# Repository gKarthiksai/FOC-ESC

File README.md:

# FOC-ESC
This is a FOC based ESC designed using open source PCB design software KiCad.

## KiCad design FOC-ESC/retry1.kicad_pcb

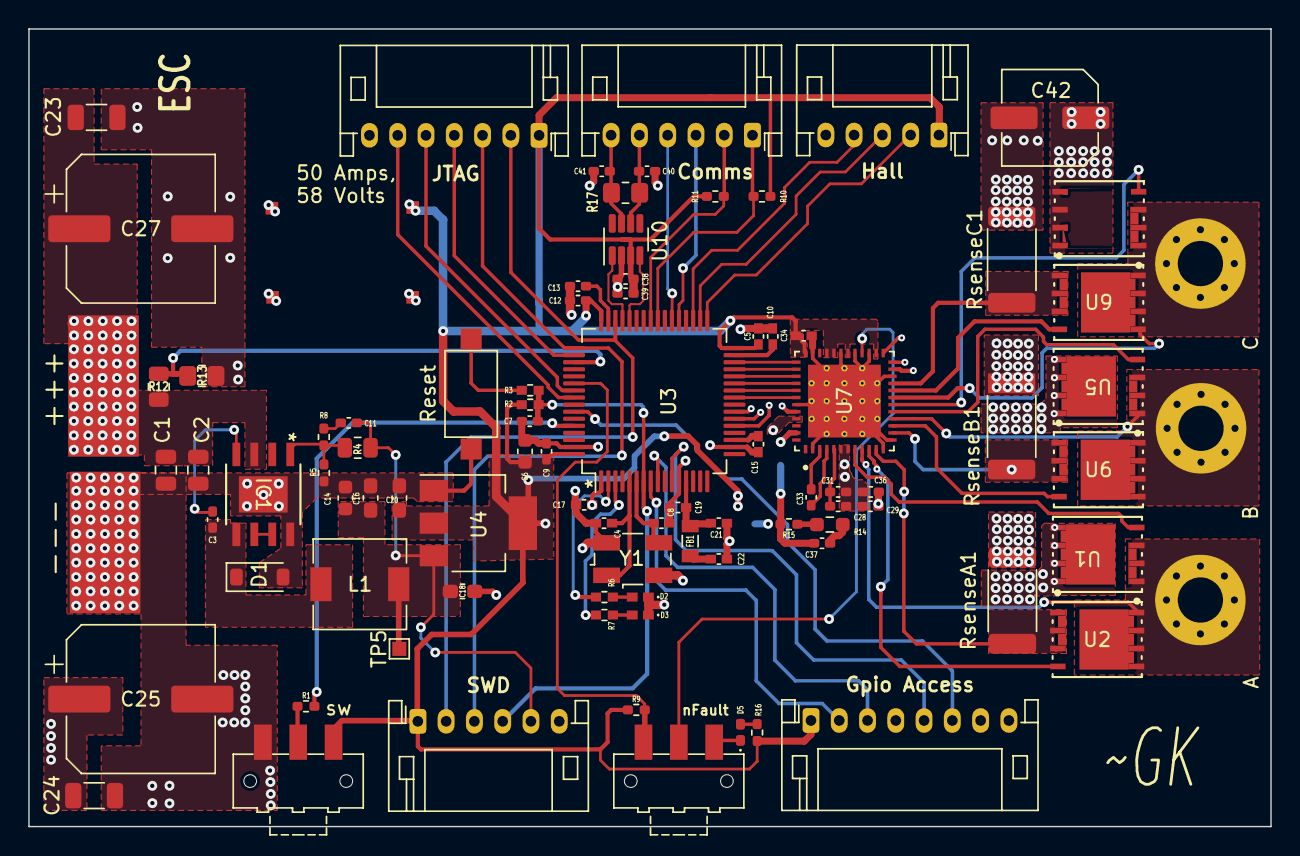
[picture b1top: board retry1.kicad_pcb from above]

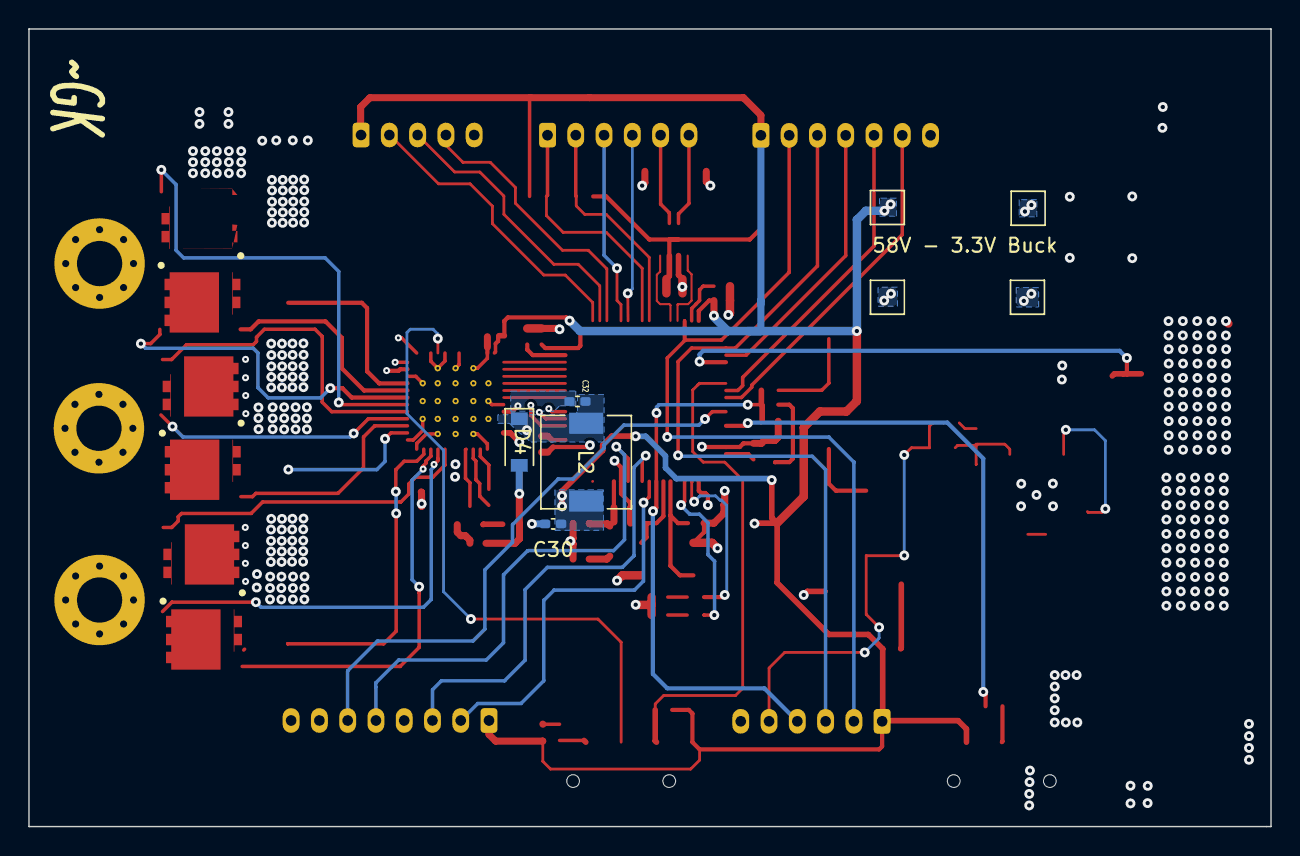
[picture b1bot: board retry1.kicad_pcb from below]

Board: 4 copper layers, 87.9 x 56.4 mm, 98 parts (8 on the bottom side), 73 nets.

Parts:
---: GND_BATT; SolderWirePad_1x01_SMD_5x10mm
A: MountingHole_Pad; MountingHole_3.2mm_M3_Pad_Via
B: MountingHole_Pad; MountingHole_3.2mm_M3_Pad_Via
C: MountingHole_Pad; MountingHole_3.2mm_M3_Pad_Via
C1, C2: 2.2uF; C_0805_2012Metric
C3, C11, C29, C32, C36, C37: 0.1uF; C_0402_1005Metric_Pad0.74x0.62mm_HandSolder
C4, C8: 10pF; C_0402_1005Metric_Pad0.74x0.62mm_HandSolder
C5, C7, C9, C12, C15, C17, C19, C38, C39, C40, C41: 100nF; C_0402_1005Metric_Pad0.74x0.62mm_HandSolder
C6, C14: 10uF; C_0603_1608Metric
C10, C13: 2.2uF; C_0402_1005Metric_Pad0.74x0.62mm_HandSolder
C16, C18, C20: 100uF; C_0603_1608Metric_Pad1.08x0.95mm_HandSolder
C21, C22, C28, C31, C34: 1uF; C_0402_1005Metric_Pad0.74x0.62mm_HandSolder
C23, C24: 470uF; C_1206_3216Metric
C25, C27: 470uF; CP_Elec_10x12.6
C30: 10uF; C_0402_1005Metric_Pad0.74x0.62mm_HandSolder
C33: 47nF; C_0402_1005Metric_Pad0.74x0.62mm_HandSolder
C42: 10uF; C_Elec_6.3x5.8
Comms: Communication Peripherials; JST_PH_S6B-PH-K_1x06_P2.00mm_Horizontal
D1: 1N4448W; D_SOD-123
D2, D3, D5: LED; LED_0402_1005Metric_Pad0.77x0.64mm_HandSolder
D4: 1N4148W; D_SOD-123
FB1: 120R; L_0805_2012Metric
Gpio Access: Digital / Analog Pins; JST_PH_S8B-PH-K_1x08_P2.00mm_Horizontal
Hall: Hall Sensors; JST_PH_S5B-PH-K_1x05_P2.00mm_Horizontal
IC1: MP9486A; SOIC-8_EP_MNP-M
J2: BATT+; SolderWirePad_1x01_SMD_5x10mm
JTAG: JATG; JST_PH_S7B-PH-K_1x07_P2.00mm_Horizontal
L1: 33uH; L_6.3x6.3_H3
L2: L; L_6.3x6.3_H3
R1, R2, R5, R9, R15, R16: 10K; R_0402_1005Metric_Pad0.72x0.64mm_HandSolder
R3: 1K; R_0402_1005Metric_Pad0.72x0.64mm_HandSolder
R4: 240K; R_0805_2012Metric
R6, R7: 330; R_0402_1005Metric_Pad0.72x0.64mm_HandSolder
R8: 4.7K; R_0402_1005Metric_Pad0.72x0.64mm_HandSolder
R10, R11: 1.8K; R_0402_1005Metric_Pad0.72x0.64mm_HandSolder
R12: 1.6K; R_0805_2012Metric
R13: 1.1K; R_0805_2012Metric_Pad1.20x1.40mm_HandSolder
R14: 150KOHM; R_0603_1608Metric_Pad0.98x0.95mm_HandSolder
R17: 120; R_0805_2012Metric_Pad1.20x1.40mm_HandSolder
Reset: SW_MEC_5G; SW_SPST_CK_RS282G05A3
RsenseA1: 1.1mOHM; R_2512_6332Metric_Pad1.40x3.35mm_HandSolder
RsenseB1: 1.1mOHM; R_2512_6332Metric_Pad1.40x3.35mm_HandSolder
RsenseC1: 1.1mOHM; R_2512_6332Metric_Pad1.40x3.35mm_HandSolder
SWD: Serial Wire Debug; JST_PH_S6B-PH-K_1x06_P2.00mm_Horizontal
TP1, TP2, TP3, TP4: TestPoint; TestPoint_Pad_2.0x2.0mm
TP5: TestPoint; TestPoint_Pad_1.0x1.0mm
U1, U2, U5, U6, U8, U9: BSC014N06NSSCATMA1; PG-WSON-8
U3: STM32F405RGTx; LQFP-64_10x10mm_P0.5mm
U4: AMS1117-3.3; SOT-223-3_TabPin2
U7: DRV8323RHRGZR; QFN50P700X700X100-49N
U10: TCAN337; TSOT-23-8
Y1: Crystal_GND2; Crystal_SMD_EuroQuartz_MJ-4Pin_5.0x3.2mm
nFault: SW_SPDT; SW_SPDT_CK-JS102011SAQN
sw: SW_SPDT; SW_SPDT_CK-JS102011SAQN

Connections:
+3.3V: C5.1, C6.1, C9.1, C12.1, C15.1, C17.1, C20.1, C22.1, C30.1, C34.2, C37.1, C38.1, C39.1, FB1.2, Gpio Access.1, Hall.1, JTAG.1, L2.1, R2.2, R9.2, R10.1, R11.1, R14.1, R16.1, SWD.1, TP3.1, U3.1 (VBAT), U3.19 (VDD), U3.32 (VDD), U3.48 (VDD), U3.64 (VDD), U4.2 (VO), U7.26 (VREF), U7.30 (IDRIVE), U7.32 (GAIN), U7.33 (ENABLE), U7.36 (DVDD), U10.3 (VCC), sw.3 (C)
+3.3VA: C19.1, C21.1, FB1.1, U3.13 (VDDA)
+5V: C11.1, C14.1, C16.1, C18.1, L1.2, R4.1, SWD.5, TP5.1, U4.3 (VI)
+BATT: C1.1, C2.1, C23.1, C24.1, C25.1, C27.1, C28.2, C29.2, C31.1, C36.2, C42.1, IC1.3 (VIN), J2.1, R12.1, TP1.1, U1.5 (DRAIN), U1.6 (DRAIN), U1.7 (DRAIN), U1.8 (DRAIN), U5.5 (DRAIN), U5.6 (DRAIN), U5.7 (DRAIN), U5.8 (DRAIN), U7.6 (VM), U7.7 (VDRAIN), U7.47 (VIN), U8.5 (DRAIN), U8.6 (DRAIN), U8.7 (DRAIN), U8.8 (DRAIN)
/BOOT0: R1.2, U3.60 (BOOT0)
/BST: C3.1, IC1.4 (BST)
/CAN_H: C41.2, Comms.6, R17.1, U10.7 (CANH)
/CAN_L: C40.1, Comms.5, R17.2, U10.6 (CANL)
/CAN_RX: U3.44 (PA11), U10.4 (RXD)
/CAN_TX: U3.45 (PA12), U10.1 (TXD)
/CB: C32.2, U7.44 (CB)
/DIM: IC1.6 (DIM), IC1.7 (EN)
/FB: IC1.1 (FB), R4.2, R5.1, R8.1
/GHA: U1.4 (GATE), U7.8 (GHA)
/GHB: U5.4 (GATE), U7.17 (GHB)
/GHC: U7.18 (GHC), U8.4 (GATE)
/GLA: U2.4 (GATE), U7.10 (GLA)
/GLB: U6.4 (GATE), U7.15 (GLB)
/GLC: U7.20 (GLC), U9.4 (GATE)
/Hall1: Hall.2, U3.33 (PB12)
/Hall2: Hall.3, U3.34 (PB13)
/Hall3: Hall.4, U3.35 (PB14)
/I2C_SCL: Comms.2, R11.2, U3.41 (PA8)
/I2C_SDA: Comms.1, R10.2, U3.40 (PC9)
/INHA: U3.30 (PB11), U7.37 (INHA)
/INHB: U3.28 (PB2), U7.39 (INHB)
/INHC: U3.26 (PB0), U7.41 (INHC)
/INLA: U3.29 (PB10), U7.38 (INLA)
/INLB: U3.27 (PB1), U7.40 (INLB)
/INLC: U3.25 (PC5), U7.42 (INLC)
/NRST: C7.1, R2.1, R3.1, SWD.4, U3.7 (NRST)
/PB6: Gpio Access.6, U3.58 (PB6)
/PC0: Gpio Access.2, U3.8 (PC0)
/PC1: Gpio Access.3, U3.9 (PC1)
/PC3: Gpio Access.5, U3.11 (PC3)
/SHA: A.1, U1.1 (SOURCE), U1.2 (SOURCE), U1.3 (SOURCE), U2.5 (DRAIN), U2.6 (DRAIN), U2.7 (DRAIN), U2.8 (DRAIN), U7.9 (SHA)
/SHB: B.1, U5.1 (SOURCE), U5.2 (SOURCE), U5.3 (SOURCE), U6.5 (DRAIN), U6.6 (DRAIN), U6.7 (DRAIN), U6.8 (DRAIN), U7.16 (SHB)
/SHC: C.1, U7.19 (SHC), U8.1 (SOURCE), U8.2 (SOURCE), U8.3 (SOURCE), U9.5 (DRAIN), U9.6 (DRAIN), U9.7 (DRAIN), U9.8 (DRAIN)
/SOA: U3.21 (PA5), U7.25 (SOA)
/SOB: U3.22 (PA6), U7.24 (SOB)
/SOC: U3.23 (PA7), U7.23 (SOC)
/SPA: RsenseA1.1, U2.1 (SOURCE), U2.2 (SOURCE), U2.3 (SOURCE), U7.11 (SPA)
/SPB: RsenseB1.1, U6.1 (SOURCE), U6.2 (SOURCE), U6.3 (SOURCE), U7.14 (SPB)
/SPC: RsenseC1.1, U7.21 (SPC), U9.1 (SOURCE), U9.2 (SOURCE), U9.3 (SOURCE)
/SW: C3.2, C32.1, D1.1 (K), D4.1 (K), IC1.5 (SW), L1.1, L2.2, U7.45 (SW)
/SWCLK/TCK: JTAG.3, SWD.3, U3.49 (PA14)
/SWDIO/TMS: JTAG.2, SWD.2, U3.46 (PA13)
/TDI: JTAG.4, U3.50 (PA15)
/TDO: JTAG.5, U3.55 (PB3)
/TRST: JTAG.6, U3.56 (PB4)
/UART_RX: Comms.4, U3.38 (PC7)
/UART_TX: Comms.3, U3.37 (PC6)
/VCP: C28.1, C31.2, U7.5 (VCP)
/Vbus: R12.2, R13.1, U3.51 (PC10)
/intopush: R3.2, Reset.2 (A)
/nFAULT: R9.1, U3.54 (PD2), nFault.1 (A)
GND: ---.1, C1.2, C2.2, C4.2, C5.2, C6.2, C7.2, C8.2, C9.2, C10.2, C12.2, C13.2, C14.2, C15.2, C16.2, C17.2, C18.2, C19.2, C20.2, C21.2, C22.2, C23.2, C24.2, C25.2, C27.2, C29.1, C30.2, C34.1, C36.1, C37.2, C38.2, C39.2, C40.2, C41.1, C42.2, D1.2 (A), D2.1 (K), D3.1 (K), D4.2 (A), Gpio Access.8, Hall.5, IC1.8 (GND), IC1.9 (GND), JTAG.7, R5.2, R13.2, R15.2, Reset.1 (A), RsenseA1.2, RsenseB1.2, RsenseC1.2, SWD.6, TP2.1, TP4.1, U3.12 (VSSA), U3.18 (VSS), U3.63 (VSS), U4.1 (GND), U7.2 (PGND), U7.12 (SNA), U7.13 (SNB), U7.22 (SNC), U7.27 (DGND), U7.29 (MODE), U7.31 (VDS), U7.35 (AGND), U7.43 (BGND), U7.49 (EP), U7.V49_1 (EP), U7.V49_2 (EP), U7.V49_3 (EP), U7.V49_4 (EP), U7.V49_5 (EP), U7.V49_6 (EP), U7.V49_7 (EP), U7.V49_8 (EP), U7.V49_9 (EP), U7.V49_10 (EP), U7.V49_11 (EP), U7.V49_12 (EP), U7.V49_13 (EP), U7.V49_14 (EP), U7.V49_15 (EP), U7.V49_16 (EP), U7.V49_17 (EP), U7.V49_18 (EP), U7.V49_19 (EP), U7.V49_20 (EP), U7.V49_21 (EP), U10.2 (GND), Y1.2, sw.1 (A)
unnamed: C11.2, R8.2
unnamed: D2.2 (A), R6.1
unnamed: D3.2 (A), R7.1
unnamed: D5.2 (A), R16.2
unnamed: D5.1 (K), nFault.3 (C)
unnamed: R1.1, sw.2 (B)
unnamed: U7.28 (NFAULT), nFault.2 (B)
unnamed: R6.2, U3.2 (PC13)
unnamed: R7.2, U3.3 (PC14)
unnamed: C4.1, U3.5 (PH0), Y1.1
unnamed: C8.1, U3.6 (PH1), Y1.3
unnamed: C10.1, U3.31 (VCAP_1)
unnamed: C13.1, U3.47 (VCAP_2)
unnamed: C33.2, U7.4 (CPH)
unnamed: C33.1, U7.3 (CPL)
unnamed: R14.2, R15.1, U7.1 (FB)
